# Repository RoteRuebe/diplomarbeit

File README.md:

Repository mit allen Files für die Diplomarbeit. An der Diplomarbeit arbeiten:

1. Lukas Lucut     (Hardware)
2. Bastian Eismann (3D - Modeling)
3. Yannick Zickler (Software)

---

# Hardware

Hier sind die Kicad - Platinendesigns von Roboter und Controller zu finden. Beide haben jeweils zwei Versionen, Rev A und Rev B.

# 3D - Modeling

Hier werden alle 3D Modelle und Cura 3D Setting sein.

# Software

Hier sind alle Codes der Diplomarbeit zu finden. Es gibt Testcodes für einzelne Module sowie die zusamengesetzten Hauptcodes

# Misc.

Außerdem sind die derzeitige Version der Diplomarbeit, Arbeitzeiterfassung (AZE) und der Projektplan hochgeladen.

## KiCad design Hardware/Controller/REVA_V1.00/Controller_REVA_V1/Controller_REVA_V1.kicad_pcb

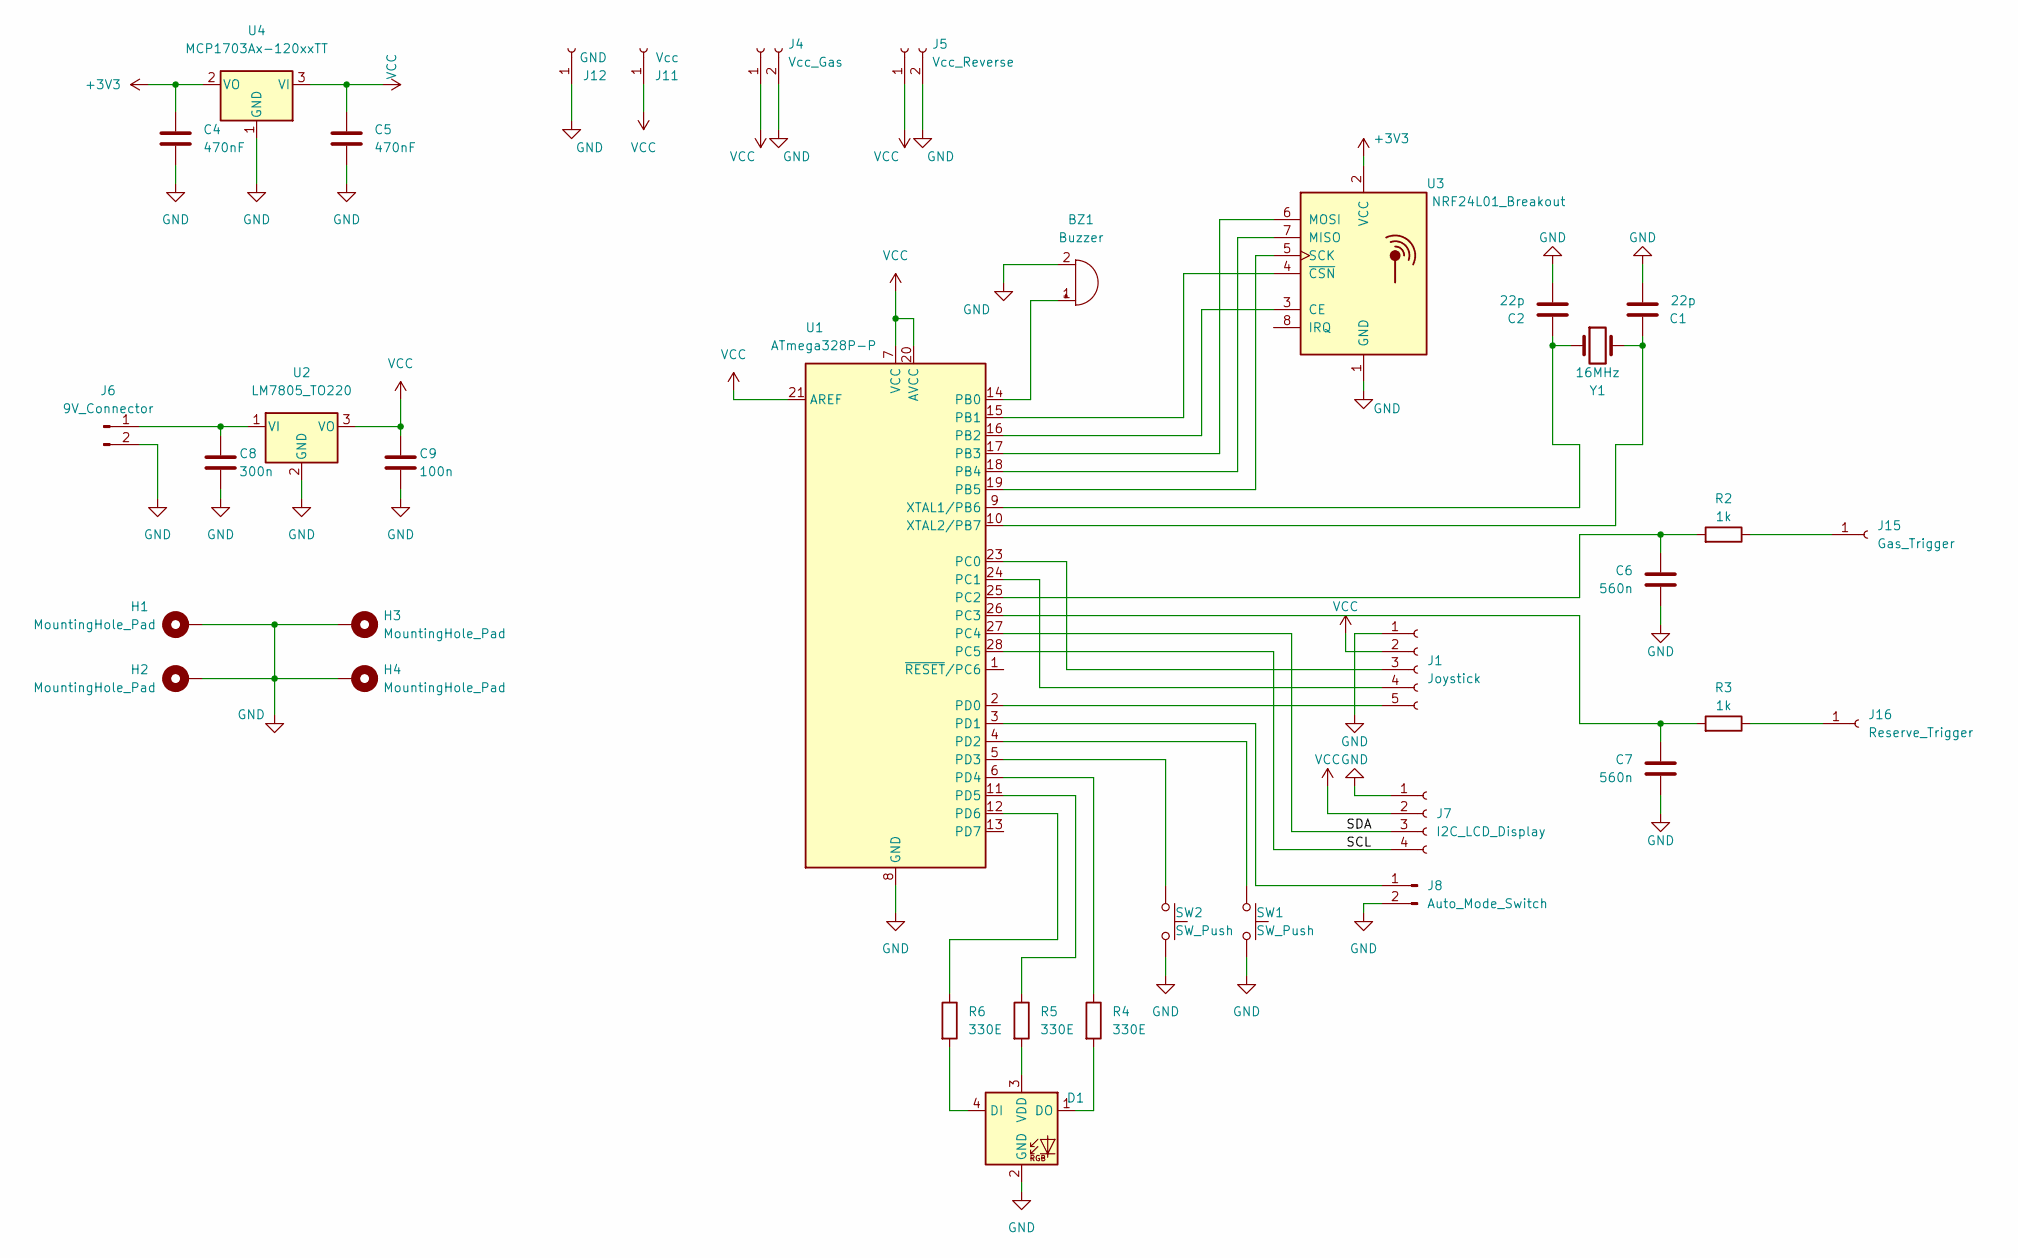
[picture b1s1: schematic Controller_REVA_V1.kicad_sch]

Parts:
BZ1: Buzzer; Buzzer_12x9.5RM7.6
C1, C2: 22p; C_1206_3216Metric
C4, C5: 470nF; C_1206_3216Metric
C6, C7: 560n; C_Disc_D12.5mm_W5.0mm_P7.50mm
C8: 300n; C_Disc_D12.5mm_W5.0mm_P7.50mm
C9: 100n; C_Disc_D12.5mm_W5.0mm_P7.50mm
D1: APA-106-F5; LED_D5.0mm-4_RGB
H1, H2, H3, H4: MountingHole_Pad; MountingHole_3.2mm_M3_Pad
J1: Joystick; PinHeader_1x05_P2.54mm_Vertical
J4: Vcc_Gas; PinHeader_1x02_P2.54mm_Vertical
J5: Vcc_Reverse; PinHeader_1x02_P2.54mm_Vertical
J6: 9V_Connector; PinHeader_1x02_P2.54mm_Vertical
J7: I2C_LCD_Display; PinHeader_1x04_P2.54mm_Vertical
J8: Auto_Mode_Switch; PinHeader_1x02_P2.54mm_Vertical
J11: Vcc; PinSocket_1x01_P2.54mm_Vertical
J12: GND; PinSocket_1x01_P2.54mm_Vertical
J15: Gas_Trigger; PinHeader_1x01_P2.54mm_Vertical
J16: Reserve_Trigger; PinHeader_1x01_P2.54mm_Vertical
R2, R3: 1k; R_Axial_DIN0411_L9.9mm_D3.6mm_P15.24mm_Horizontal
R4, R5, R6: 330E; R_1206_3216Metric
SW1, SW2: SW_Push; SW_PUSH-12mm_Wuerth-430476085716
U1: ATmega328P-P; DIP-28_W7.62mm
U2: LM7805_TO220; TO-220-3_Vertical
U3: NRF24L01_Breakout; nRF24L01_Breakout
U4: MCP1703Ax-120xxTT; SOT-23
Y1: 16MHz; Crystal_HC49-4H_Vertical

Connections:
+3V3: C4.1, U3.2 (VCC), U4.2 (VO)
/SCL: J7.4, U1.28 (PC5)
/SDA: J7.3, U1.27 (PC4)
GND: BZ1.2 (+), C1.2, C2.2, C4.2, C5.2, C6.2, C7.2, C8.2, C9.2, D1.2 (GND), H1.1, H2.1, H3.1, H4.1, J1.1, J4.2, J5.2, J6.2, J7.1, J8.2, J12.1, SW1.2, SW2.2, U1.8 (GND), U1.22 (GND), U2.2 (GND), U3.1 (GND), U4.1 (GND)
unnamed: BZ1.1 (-), U1.14 (PB0)
unnamed: C1.1, U1.10 (XTAL2/PB7), Y1.2
unnamed: C2.1, U1.9 (XTAL1/PB6), Y1.1
unnamed: C6.1, R2.2, U1.25 (PC2)
unnamed: C7.1, R3.2, U1.26 (PC3)
unnamed: C8.1, J6.1, U2.1 (VI)
unnamed: D1.1 (DO), R4.2
unnamed: D1.3 (VDD), R5.2
unnamed: D1.4 (DI), R6.2
unnamed: J1.3, U1.23 (PC0)
unnamed: J1.4, U1.24 (PC1)
unnamed: J1.5, U1.2 (PD0)
unnamed: J8.1, U1.3 (PD1)
unnamed: J15.1, R2.1
unnamed: J16.1, R3.1
unnamed: R4.1, U1.6 (PD4)
unnamed: R5.1, U1.11 (PD5)
unnamed: R6.1, U1.12 (PD6)
unnamed: SW1.1, U1.4 (PD2)
unnamed: SW2.1, U1.5 (PD3)
unnamed: U1.15 (PB1), U3.4 (~CSN)
unnamed: U1.16 (PB2), U3.3 (CE)
unnamed: U1.17 (PB3), U3.6 (MOSI)
unnamed: U1.18 (PB4), U3.7 (MISO)
unnamed: U1.19 (PB5), U3.5 (SCK)
VCC: C5.1, C9.1, J1.2, J4.1, J5.1, J7.2, J11.1, U1.7 (VCC), U1.20 (AVCC), U1.21 (AREF), U2.3 (VO), U4.3 (VI)

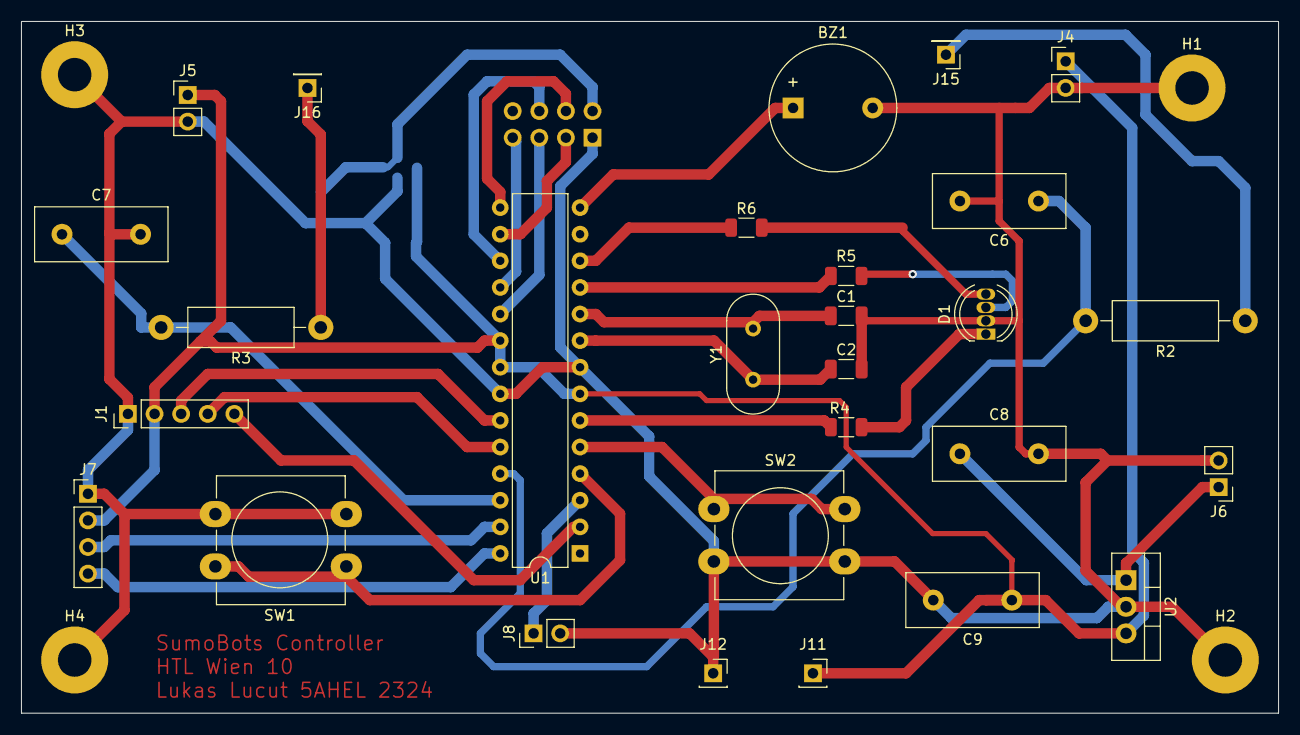
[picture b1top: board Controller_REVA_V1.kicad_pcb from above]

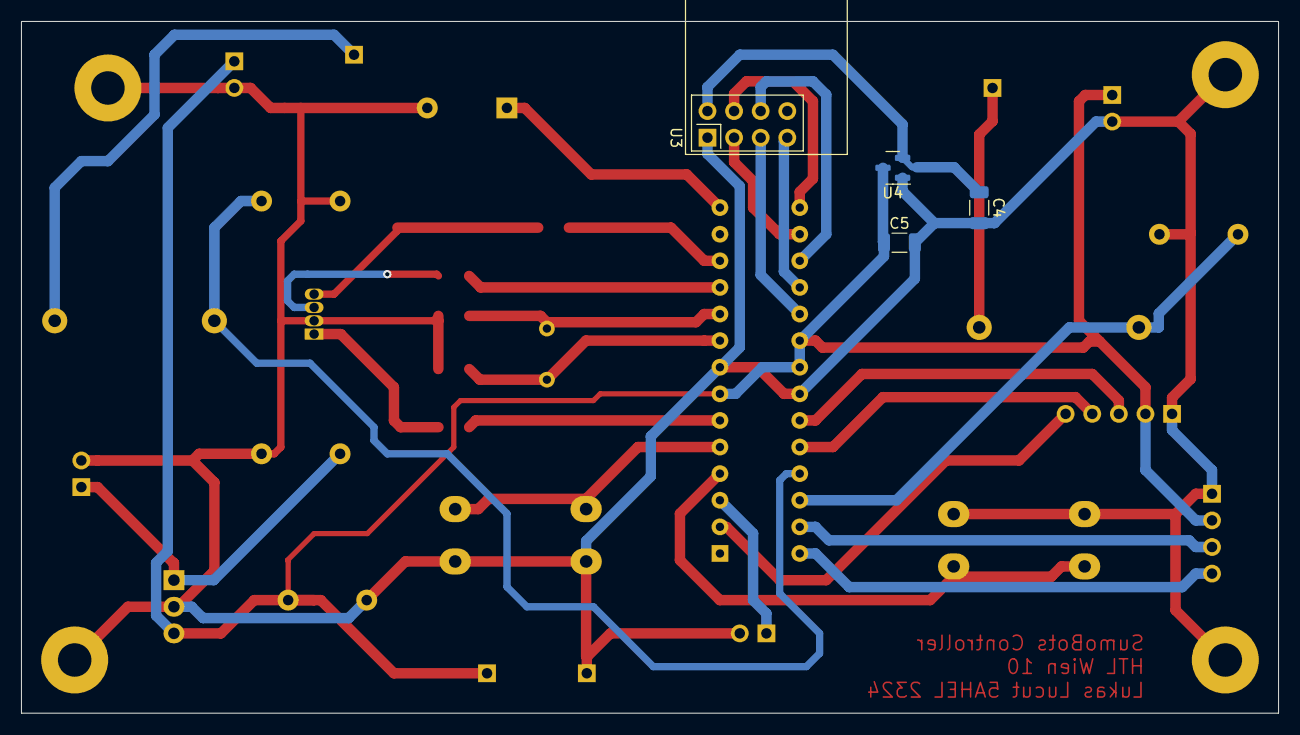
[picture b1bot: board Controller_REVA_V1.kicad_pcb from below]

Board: 2 copper layers, 120.0 x 66.0 mm, 36 parts (4 on the bottom side), 30 nets.

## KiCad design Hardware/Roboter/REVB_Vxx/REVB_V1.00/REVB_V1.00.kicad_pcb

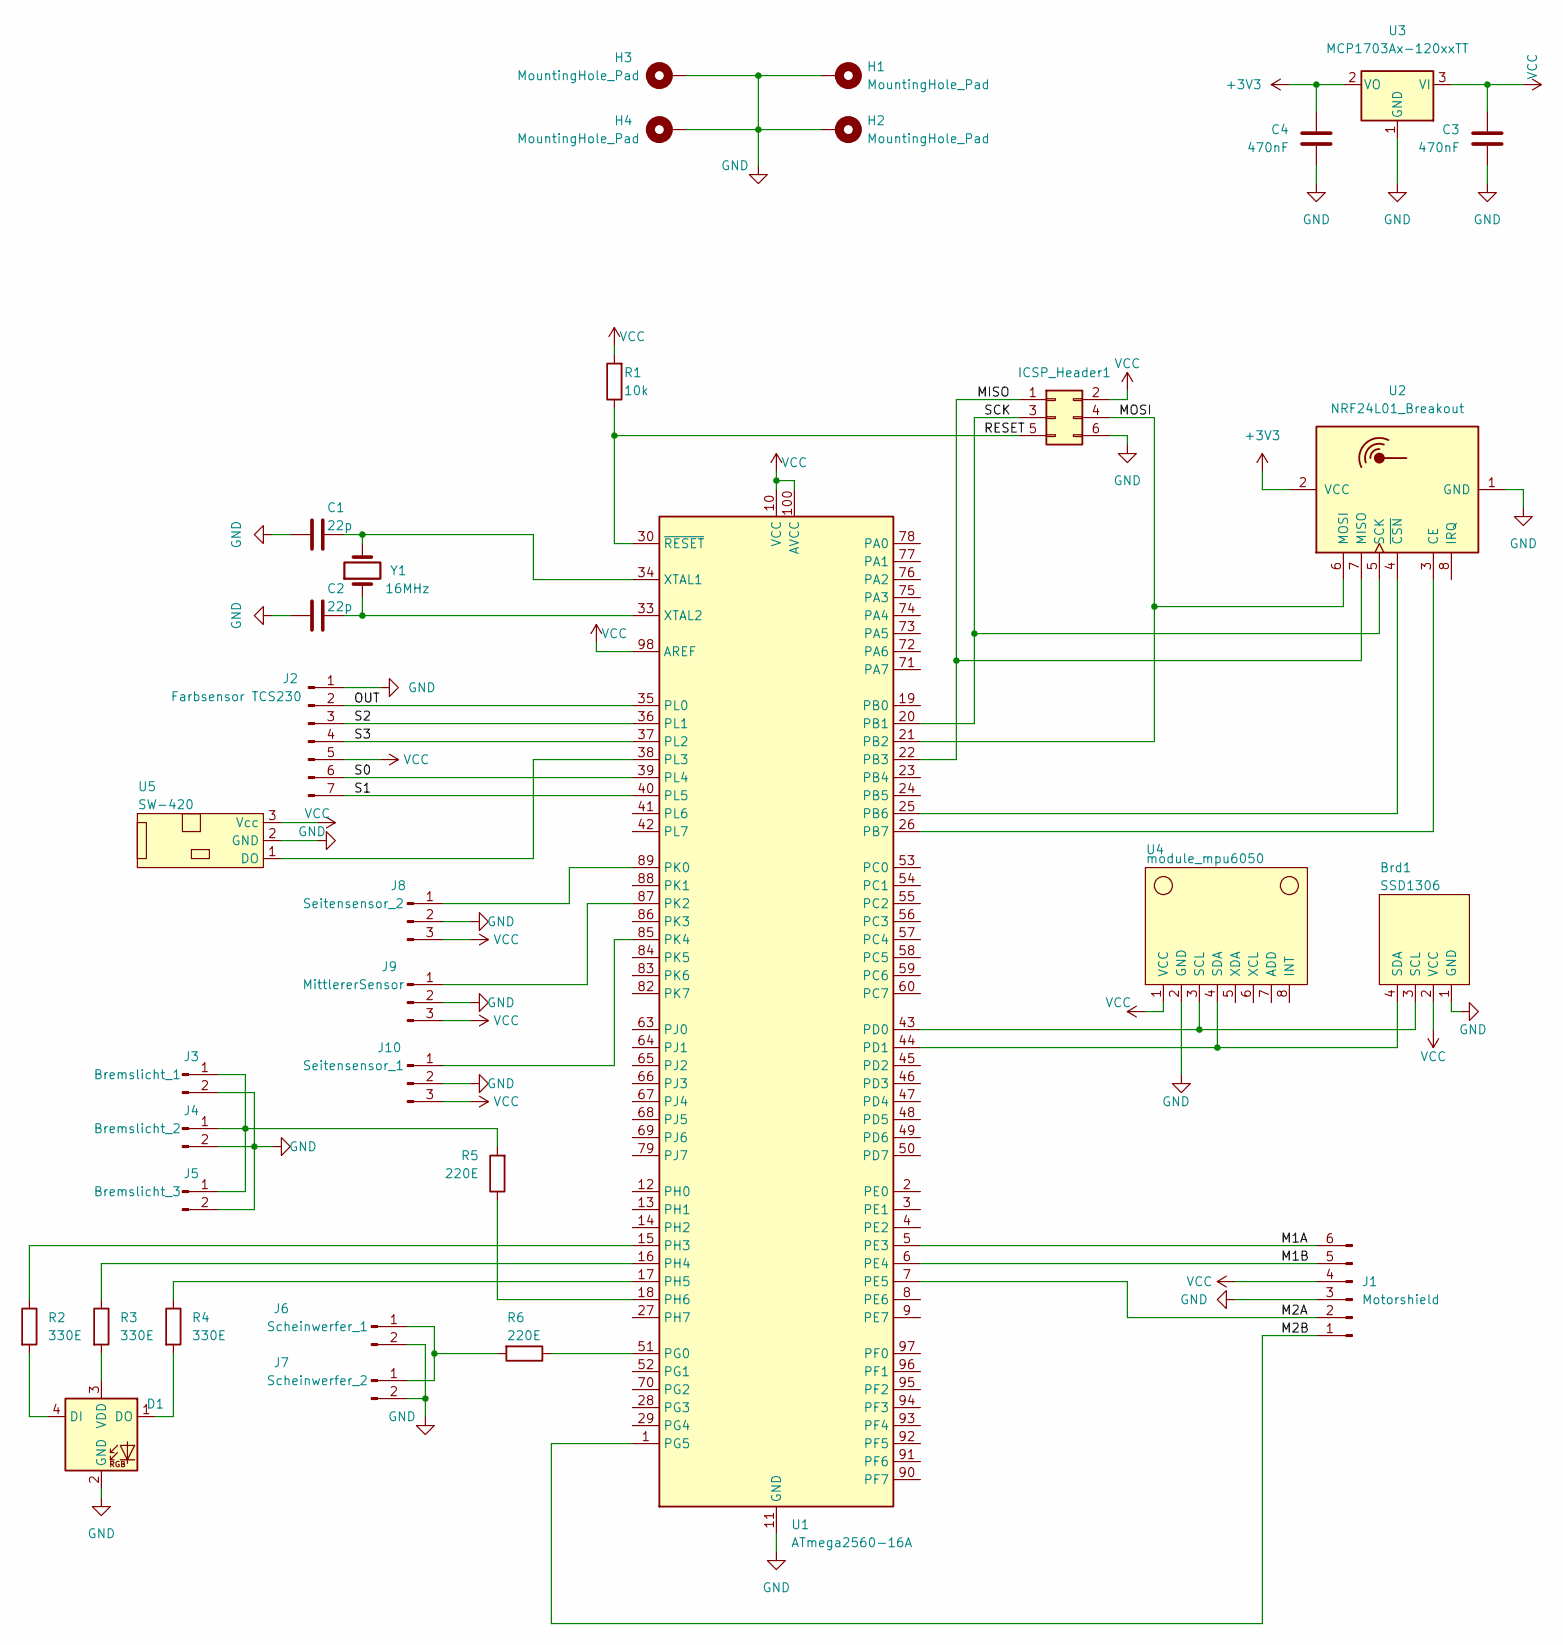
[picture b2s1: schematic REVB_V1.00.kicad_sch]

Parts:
Brd1: SSD1306; PinSocket_1x04_P2.54mm_Vertical
C1, C2: 22p; C_1206_3216Metric
C3, C4: 470nF; C_1206_3216Metric
D1: APA-106-F5; LED_D5.0mm-4_RGB
H1, H2, H3, H4: MountingHole_Pad; MountingHole_3.2mm_M3_Pad
ICSP_Header1: Conn_02x03_Odd_Even; PinHeader_2x03_P2.54mm_Vertical
J1: Motorshield; PinHeader_1x06_P2.54mm_Vertical
J2: Farbsensor TCS230; PinHeader_1x07_P2.54mm_Vertical
J3: Bremslicht_1; PinHeader_1x02_P2.54mm_Vertical
J4: Bremslicht_2; PinHeader_1x02_P2.54mm_Vertical
J5: Bremslicht_3; PinHeader_1x02_P2.54mm_Vertical
J6: Scheinwerfer_1; PinHeader_1x02_P2.54mm_Vertical
J7: Scheinwerfer_2; PinHeader_1x02_P2.54mm_Vertical
J8: Seitensensor_2; PinHeader_1x03_P2.54mm_Vertical
J9: MittlererSensor; PinHeader_1x03_P2.54mm_Vertical
J10: Seitensensor_1; PinHeader_1x03_P2.54mm_Vertical
R1: 10k; R_1206_3216Metric
R2, R3, R4: 330E; R_1206_3216Metric
R5, R6: 220E; R_1206_3216Metric
U1: ATmega2560-16A; TQFP-100_14x14mm_P0.5mm
U2: NRF24L01_Breakout; nRF24L01_Breakout
U3: MCP1703Ax-120xxTT; SOT-23
U4: module_mpu6050
U5: SW-420
Y1: 16MHz; Crystal_HC49-4H_Vertical

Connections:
+3V3: C4.1, U2.2 (VCC), U3.2 (VO)
/M1A: J1.6, U1.5 (PE3)
/M1B: J1.5, U1.6 (PE4)
/M2A: J1.2, U1.7 (PE5)
/M2B: J1.1, U1.1 (PG5)
/MISO: ICSP_Header1.1, U1.22 (PB3), U2.7 (MISO)
/MOSI: ICSP_Header1.4, U1.21 (PB2), U2.6 (MOSI)
/OUT: J2.2, U1.35 (PL0)
/RESET: ICSP_Header1.5, R1.1, U1.30 (~RESET)
/S0: J2.6, U1.39 (PL4)
/S1: J2.7, U1.40 (PL5)
/S2: J2.3, U1.36 (PL1)
/S3: J2.4, U1.37 (PL2)
/SCK: ICSP_Header1.3, U1.20 (PB1), U2.5 (SCK)
GND: Brd1.1 (GND), C1.2, C2.2, C3.2, C4.2, D1.2 (GND), H1.1, H2.1, H3.1, H4.1, ICSP_Header1.6, J1.3, J2.1, J3.2, J4.2, J5.2, J6.2, J7.2, J8.2, J9.2, J10.2, U1.11 (GND), U1.32 (GND), U1.62 (GND), U1.81 (GND), U1.99 (GND), U2.1 (GND), U3.1 (GND), U4.2 (GND), U5.2 (GND)
unnamed: Brd1.3 (SCL), U1.43 (PD0), U4.3 (SCL)
unnamed: Brd1.4 (SDA), U1.44 (PD1), U4.4 (SDA)
unnamed: C1.1, U1.34 (XTAL1), Y1.2
unnamed: C2.1, U1.33 (XTAL2), Y1.1
unnamed: D1.1 (DO), R4.2
unnamed: D1.3 (VDD), R3.2
unnamed: D1.4 (DI), R2.2
unnamed: J3.1, J4.1, J5.1, R5.2
unnamed: J6.1, J7.1, R6.2
unnamed: J9.1, U1.87 (PK2)
unnamed: J10.1, U1.85 (PK4)
unnamed: R2.1, U1.15 (PH3)
unnamed: R3.1, U1.16 (PH4)
unnamed: R4.1, U1.17 (PH5)
unnamed: R5.1, U1.18 (PH6)
unnamed: R6.1, U1.51 (PG0)
unnamed: U1.25 (PB6), U2.4 (~CSN)
unnamed: U1.26 (PB7), U2.3 (CE)
unnamed: U1.38 (PL3), U5.1 (DO)
unnamed: J8.1, U1.89 (PK0)
VCC: Brd1.2 (VCC), C3.1, ICSP_Header1.2, J1.4, J2.5, J8.3, J9.3, J10.3, R1.2, U1.10 (VCC), U1.31 (VCC), U1.61 (VCC), U1.80 (VCC), U1.98 (AREF), U1.100 (AVCC), U3.3 (VI), U4.1 (VCC), U5.3 (Vcc)

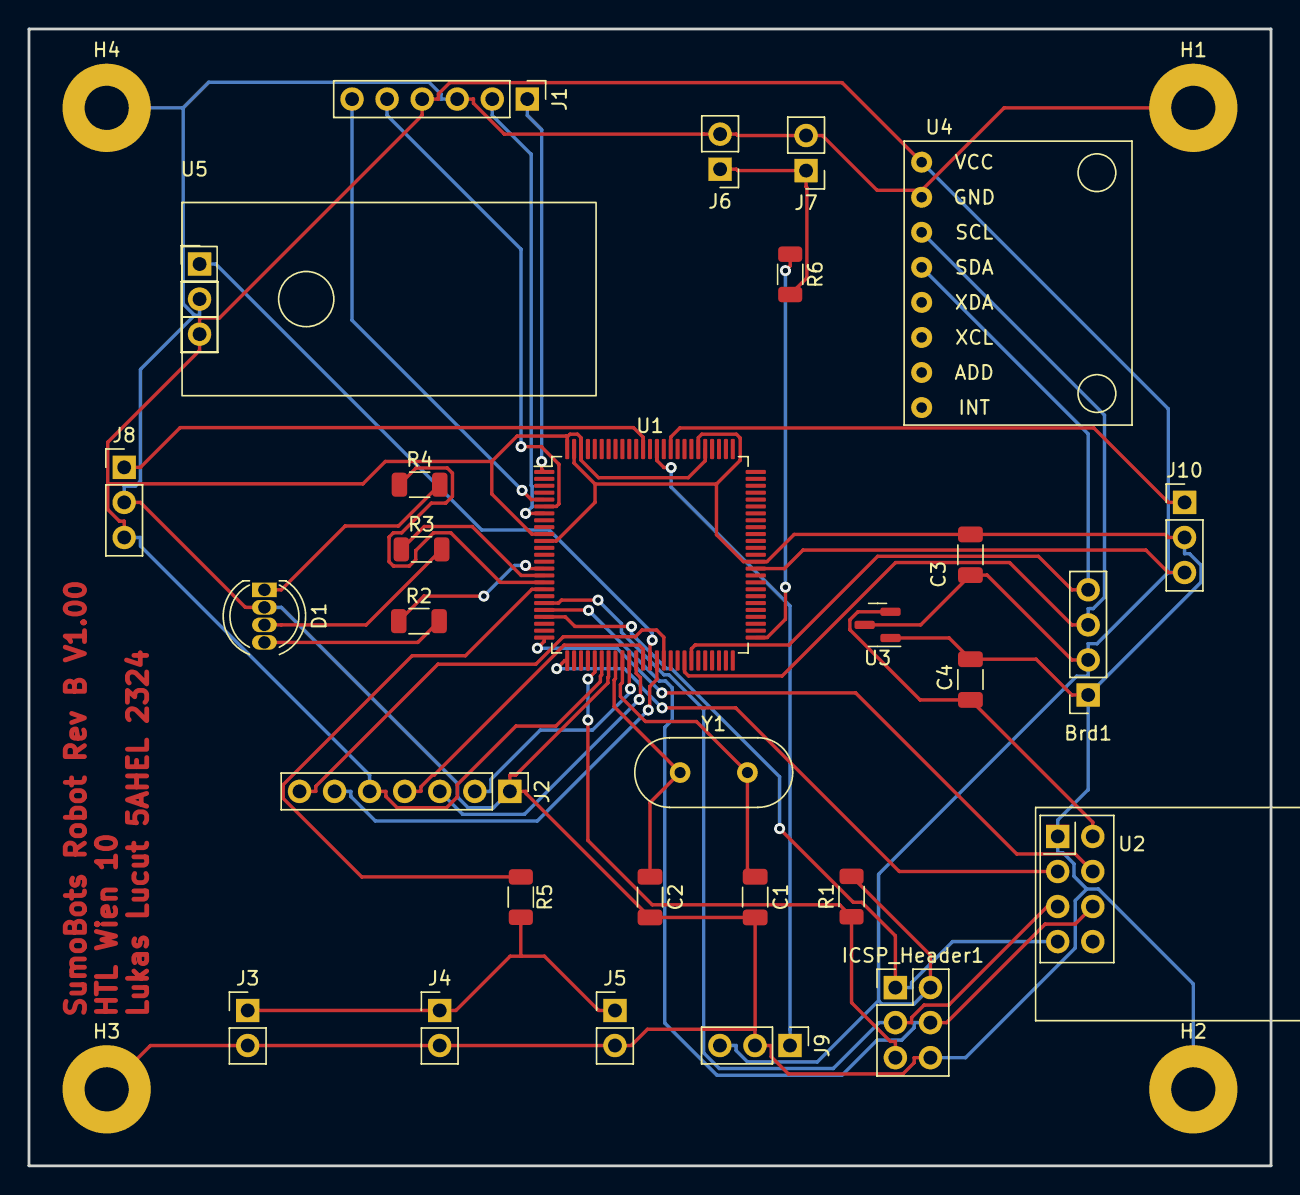
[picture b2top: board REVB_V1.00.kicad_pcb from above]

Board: 2 copper layers, 90.0 x 82.4 mm, 33 parts (0 on the bottom side), 36 nets.

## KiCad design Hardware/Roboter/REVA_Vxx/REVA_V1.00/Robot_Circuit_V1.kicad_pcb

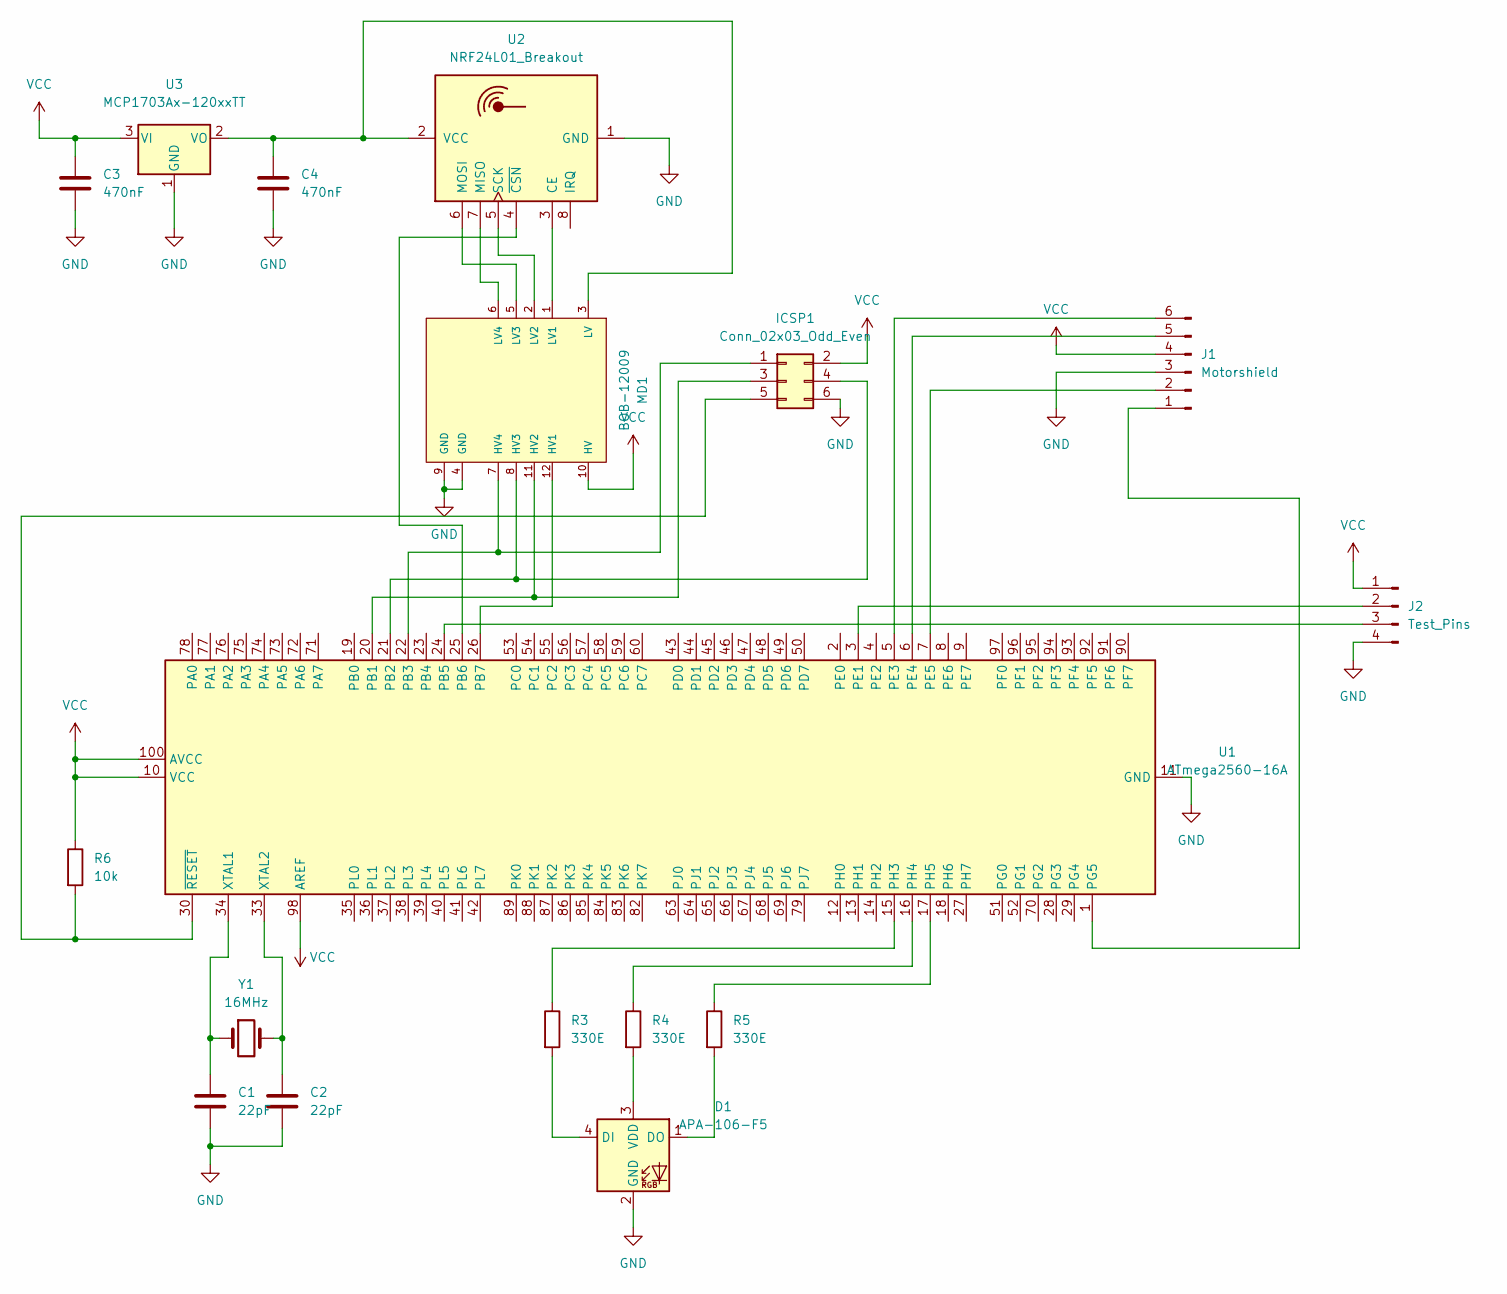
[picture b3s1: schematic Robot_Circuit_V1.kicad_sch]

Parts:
C1, C2: 22pF; C_1206_3216Metric
C3, C4: 470nF; C_1206_3216Metric
D1: APA-106-F5; LED_D5.0mm-4_RGB
ICSP1: Conn_02x03_Odd_Even; PinHeader_2x03_P2.54mm_Vertical
J1: Motorshield; PinHeader_1x06_P2.54mm_Vertical
J2: Test_Pins; PinSocket_1x04_P2.54mm_Vertical
MD1: BOB-12009; SparkFun-BOB-12009-MFG; mouser part number 474-BOB-12009; digikey description LOGIC LEVEL CONVERTER - BI-DIREC
R3, R4, R5: 330E; R_1206_3216Metric
R6: 10k; R_1206_3216Metric
U1: ATmega2560-16A; TQFP-100_14x14mm_P0.5mm
U2: NRF24L01_Breakout; nRF24L01_Breakout
U3: MCP1703Ax-120xxTT; SOT-23
Y1: 16MHz; Crystal_HC49-U_Vertical

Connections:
unnamed: C1.1, U1.34 (XTAL1), Y1.1
unnamed: C2.1, U1.33 (XTAL2), Y1.2
unnamed: C4.1, MD1.3 (LV), U2.2 (VCC), U3.2 (VO)
unnamed: D1.1 (DO), R5.2
unnamed: D1.3 (VDD), R4.2
unnamed: D1.4 (DI), R3.2
unnamed: ICSP1.1, MD1.7 (HV4), U1.22 (PB3)
unnamed: ICSP1.3, MD1.11 (HV2), U1.20 (PB1)
unnamed: ICSP1.4, MD1.8 (HV3), U1.21 (PB2)
unnamed: ICSP1.5, R6.2, U1.30 (~RESET)
unnamed: J1.1, U1.1 (PG5)
unnamed: J1.2, U1.7 (PE5)
unnamed: J1.5, U1.6 (PE4)
unnamed: J1.6, U1.5 (PE3)
unnamed: J2.2, U1.3 (PE1)
unnamed: J2.3, U1.24 (PB5)
unnamed: MD1.1 (LV1), U2.3 (CE)
unnamed: MD1.2 (LV2), U2.5 (SCK)
unnamed: MD1.5 (LV3), U2.6 (MOSI)
unnamed: MD1.6 (LV4), U2.7 (MISO)
unnamed: MD1.12 (HV1), U1.26 (PB7)
unnamed: R3.1, U1.15 (PH3)
unnamed: R4.1, U1.16 (PH4)
unnamed: R5.1, U1.17 (PH5)
unnamed: U1.25 (PB6), U2.4 (~CSN)
VCC: C3.1, ICSP1.2, J1.4, J2.1, MD1.10 (HV), R6.1, U1.10 (VCC), U1.31 (VCC), U1.61 (VCC), U1.80 (VCC), U1.98 (AREF), U1.100 (AVCC), U3.3 (VI)

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
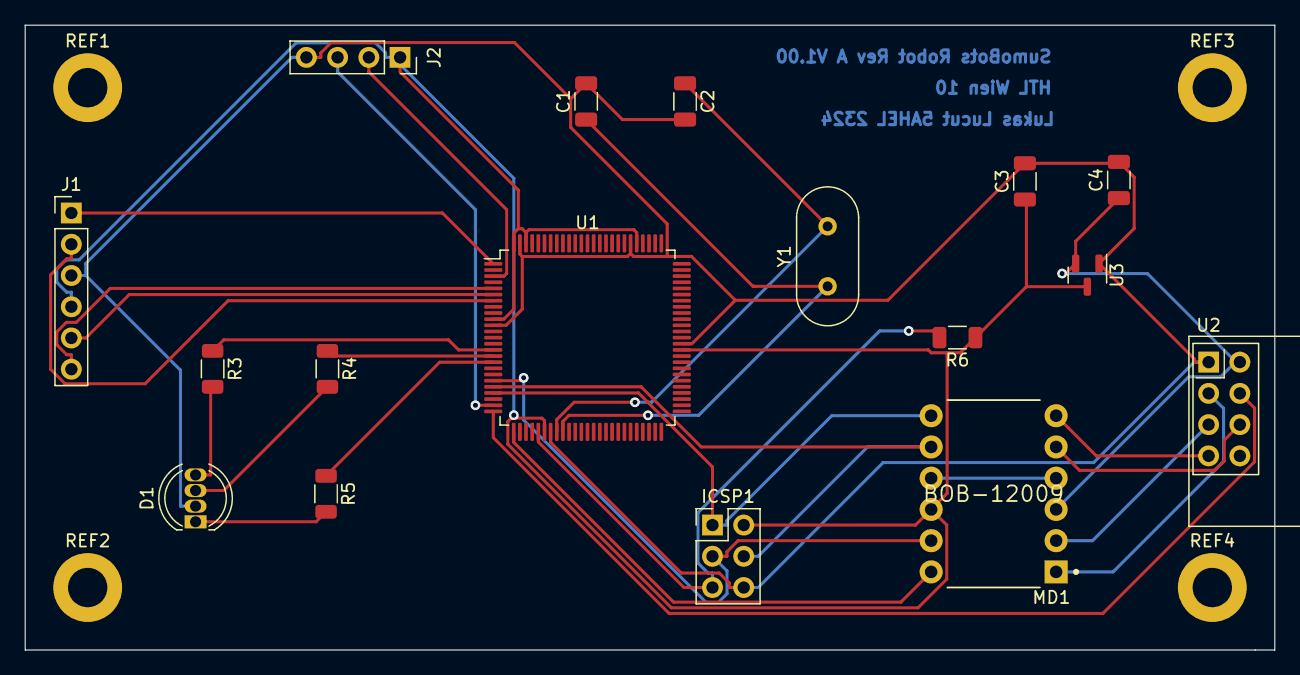
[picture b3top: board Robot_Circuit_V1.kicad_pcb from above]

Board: 2 copper layers, 101.6 x 50.8 mm, 21 parts (0 on the bottom side), 28 nets.

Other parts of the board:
REF1, REF2, REF3, REF4: MountingHole_3.2mm_M3_DIN965_Pad

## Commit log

2023-12-11 Initial Commit - moving files from google drive to github
2023-12-11 Cleaning up and adding "Projektplan"
2023-12-12 test Zugriffsberechtigung
2023-12-12 neue Inhalte Quarzoszillator
2023-12-14 Neue Dokumentation
2023-12-14 Kapitel 6 Begonnen
2023-12-14 Codes updaten für Kommunikation mit zentralem Server
2023-12-15 Cleaning up code, adding header file
2023-12-15 neue Überschriften, HW-Teil
2023-12-15 bearbeitete Version
2023-12-15 AZE, stand 15.12.2023 13:53
2023-12-15 Kleine Verbesserung
2023-12-15 neue Projektstatusdoku. für Projektlibre
2023-12-15 Weekly-Report-System neu aufgesetzt, jeden Samstag wird die neuste Datei abgegeben
2023-12-15 PLA Dokumentation
2023-12-15 Fehler Ausgebessert 3D-Design
2023-12-16 +3D-Modell Zeug UwU
2023-12-16 Weekly Report 10 auch hier lmao
2023-12-16 NRF24L01+ Teil fertiggeschrieben, wird 16.12.2023 abgegeben
2023-12-16 abgegeben, 16-12-2023
2023-12-16 Fehler ausgebessert
2023-12-26 AZE aktualisiert
2023-12-27 AZE aktualisiert, Rev B fertig und Zatl geschickt (27.12.2023, 18:24:21)
2023-12-27 AZE nochmal, hab was vergessen
2024-01-07 Dokumentation, HW -> Rev A fertig dokumentiert, Rev B Blockschaltbild hinzugefügt
2024-01-09 Rev B Dokumentation, noch nicht fertig fehlt bissl was
2024-01-09 HW-Teil erweitert yuuhuu
2024-01-09 3D Material Fertig
2024-01-12 HW-Teil, Rev B PCB Kapitel fertig :)
2024-01-13 Add files via upload
    Kleine Überarbeitung
2024-01-13 Server code
2024-01-13 AZE stand 19:32:49, 13:01:2024
2024-01-13 DA umbenannt
2024-01-15 Mehr 3 D Print 👌
2024-01-15 Version gerettet <3
2024-01-19 code verschieben
2024-01-19 Updated text.jpg
2024-01-19 Neue Version lmao
2024-01-20 abgegeben
2024-01-20 alte version le deleted
2024-01-22 Zatl korrigierte Version 1.3
2024-01-23 no message
2024-01-25 testetetet
2024-01-26 Deleting useless files
2024-01-26 Uploading server code
2024-01-26 I2C-Bus
2024-01-26 Deleting log files, new Server code
2024-01-26 New Robo code
2024-01-28 More comments
2024-01-28 Das internet ist fuer uns alle neuland. Erweiterung website
2024-01-28 Very minor fix
2024-01-28 Neues icon
2024-01-28 Rounded boxes!
2024-01-30 Neuer server code. Nicht fertig, Roboter code muss angepasst werden. Außerdem: pfadänderung der logs noch nicht in allen codes übernommen.
2024-01-31 AZE aktualisiert 😎, verbesserte Version der DA hochgeladen 🦁
2024-02-02 Reverting prev Commit.
2024-02-02 Revert "Reverting prev Commit." ups.
    This reverts commit 57b0e3b5c6768b9112b4db4ac3e3c5eee2560ce9.
2024-02-02 anpassung map funktion auf fmap. verbindung zw. roboter und controller und roboter und server funktioniert noch nicht gleichzeitig, jetzt verbindung zw. roboter und server auskommentiert. typecasting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
2024-02-03 Files umbennant. Roboter code refactored Alle Files wurden auf lowercase gestellt
    Roboter Code Reihenfolge von Read / Write und stopListening umgestellt. Vielleicht geht das ja jetzt. Auserdem Aenderung Read pipe von 0 auf 1. Funktioniert read() und isAvailable() trotzdem gleich?
    Refactoring von Variablennamen, Ort der Deklaration in roboter.ino und roboter.h
2024-02-03 Upload der Aenderungen des letzten commits
2024-02-03 AZE aktualisiert, Farbsensor und OLED-Display dokumentiert
2024-02-08 korrigierte Version von ZATL
2024-02-08 AZE aktualisiert 😜, Infrarotsensor dokumentiert Komponente von Rev B sind fertig
2024-02-10 AZE aktualisiert, WR 20
2024-02-10 Quellenverzeichnis/Literaturverzeichnis befüllt, Schaltungen u. PCB in Anhängen hinzugefügt
2024-02-13 Bug fixes
    Version geht noch immer nicht
2024-02-13 Bugfixes
    Berechnung für Motorsteuerung. Kom. hatte Fehler, nun auskommentiert.
2024-02-15 AZE aktualisiert 🔞
2024-02-16 Salvation
    Kom. mit Server und Controller funktioniert gleichzeitig. So kompliziert war die Lösung eh nicht 🙃
2024-02-16 Debug statement gelöscht
2024-02-16 Implementierung Gyroskop. Noch nicht vollständig
2024-02-16 PM-Dokumentation wurde gestartet --> Sotftwareverwaltung via Git
2024-02-16 AZE aktualisiert Never gonna Give u up 🤣
2024-02-17 AZE optisch bearbeitet, Diplomarbeit PM-Teil umformuliert
2024-02-18 DA V1.6 Korrektur
2024-02-18 Dokumentation Server und Protokoll zw. Roboter und Server. Hinzufügung der Codes in den Anhang
2024-02-18 Änderung von Zatl, Kapitel 9.2
2024-02-19 Code: Implementation Gyroskop
    Änderung von Server und Roboter Code. Noch ungetestet.
2024-02-19 Neues Cooles Kapitel
2024-02-19 Code: Bugfixes in implementierung von Gyroskop
    Problem: Im Gyroskop Datenpacket werden zu viele Bytes gesendet, das RF24 Modul kann max. 32 senden.
    To Do: Aufteilen des Packets in Acc, Gyro und Temp um das zu vermeiden
2024-02-19 Bugfixes für Gyroskop Roboter-seitig
2024-02-19 Code: Bugfix Gyroskop
    Die Packete des Gyroskops werden aufgeteilt, um das 32 Byte-limit des RF24 Moduls nicht zu erreichen.
2024-02-19 Code: Weis nicht mehr. Iwas gyroskop diagram usw.
2024-02-19 Code: mini Änderung jo
2024-02-19 kurz was umgeschrieben 😐
2024-02-20 Code: Sensor data are floats not ints now
2024-02-20 Code: Einige Änderungen in Roboter
    1. Array wird zwischen jedem Versenden mit clearDataArray komplett gelöscht.
    2. Check, ob Gyro auch angeschlossen wurde -> Fehler in Elektronik wurde aufgedeckt
    3. LED wird runtime geupdated, wenn er sich mit dem Server verbindet
2024-02-20 Gyrskop eingeführt
2024-02-20 Einen Satz geschrieben 😋
2024-02-20 Neue Inhalte in DA: softwareteil
2024-02-20 AZE (auf Gönnungtour) aktualisiert, Controller Blockschaltbild eingefügt
2024-02-21 Neue INhalte Software
2024-02-22 Neue inhalte DA + kinderliechte kuhle kopfzeile
2024-02-22 AZE aktualisiert :^)
2024-02-23 flask server squash later
2024-02-23 Anstelle von python, txt files und php gibt es jetzt einen Multithreaden Flask Server
2024-02-23 Now running 1 Multithreaded Python Flask server instead of python for rf24 + php for webserver
2024-02-23 Revert "merging"
    This reverts commit bf34cdf9def5635425216a1e9576eeff1efccdaf, reversing
    changes made to 7d91e4d6d1b951679c960df9d1e7a7bc1c21a0f7.
2024-02-23 Renaming index.php to index.html
2024-02-23 Deleting index.php
2024-02-23 AZE und DA Dokumentation
2024-02-24 Code: Verbesserung Server Flask Server returned jetzt Daten. Diese kommen aus dem deque, welche hier als Ringpuffer verwendet werden Die Daten sind nichtmehr Textfiles sondern JSON
    Client Seitig sind die Requests jetzt asynchron, deswegen braucht es die callback funktionen
    Um nicht 20 callback funktionen zu haben, werden gyro xyz und acc xyz jetzt gleichzeitig abgefragt, was eh mehr sinn macht.
    Das heißt, server returned jetzt 2d array bei /data/gyro oder /acc. ahja statt /log gibt es jetzt /data
2024-02-24 Fixing typos
2024-02-24 Code: /data returns dict not 2d array. style.css fixed identation. replaced write_log with array.append. Added /about page
2024-02-26 AZE aktualisiert stand 26.02.2024
2024-02-27 Code: Minor changes to website
2024-02-28 Null bytes entfernen. Charts jetzt mit 10 fps.
2024-02-28 Graph jetzt 10 fps
2024-02-28 AZE aktualisiert 😎
2024-02-29 Version 2.1
2024-03-01 Code: Adding robotConnected to dashboard
2024-03-01 Small bugfix
2024-03-01 Code: Controller Anzeige implementiert
2024-03-01 AZE und HW-Teil erweitert
2024-03-03 Änderungen Server 1. Navbar hinzugefügt 2. Ein Diagramm entfernt 3. Tweaking einiger Margins, Colors etc.
2024-03-03 Neue Inhalte Software sowie kleine Änderungen Code
2024-03-03 Änderung pos. HTL logo
2024-03-04 AZE für Week 27 geöffnet, Montag eingetragen
2024-03-05 korrigierte Version von ZATL V1.8, noch zwei Versionen bis Sense ☠
2024-03-06 Controller setup protokoll
2024-03-06 AZE aktualisiert 😶
2024-03-07 AZE aktualisiert 😋
2024-03-08 HW-Controller und Doc.
2024-03-09 Added RGB-Spport for controller
2024-03-09 HW-Teil fertiggeschrieben (Raspi Zero u. ESP32 fehlt, wird bei korrekte Inbetriebnahme Dok.)
2024-03-12 Projektarchitektur u. Danksagung verfasst
2024-03-13 "upgedatet"
2024-03-14 AZE aktualisiert & Sensornutzen dokumentiert
2024-03-15 AZE + Dok
2024-03-18 DA Version 2.0 letzter Lauf
2024-03-18 Dok. + AZE
2024-03-19 Dokumentation :)
2024-03-19 HW-Dokumentation auf den neusten Stand
2024-03-20 AZE aktualisiert, Dok: PCB u. Circuit im Anhang, neues OSP
2024-03-20 Deleting debug msg controller.ino
2024-03-21 Channel, pipe as arg for multithreading
2024-03-21 Adding support for multiple robots/ controllers, make sendSensorData non-blocking
2024-03-21 Documentation channels / pipes
2024-03-21 AZE aktualisiert, Dokumentation: neues PSP, Roboter Rev A fertig, Controller Rev A fertig --> Rev B finale Ergebnisse mit Sensoren
2024-03-22 Small bugfixes
2024-03-22 Neue Inhalte
2024-03-22 Änderungen für Zulassung mehrerer Roboter
2024-03-22 Moving files
    Adding files back again
2024-03-23 AZE homies
2024-03-23 Neue Inhalte DA
2024-03-23 Support für mehrere Roboter in Website implementiert
2024-03-23 Deleting startup.sh
2024-03-23 Umbennenung pipes
2024-03-24 AZE++; Dok: PM-Inhalte, neues Abstract; Bedienungsanleitung: Draft
2024-03-24 HW-Teil 100% fertig u. formatiert, Unterüberschriften korrigiert, Endergebnisse DRAFT gestartet
2024-03-26 Frequenzmultiplex - es geht aber nicht sehr gut
2024-03-26 Frequenzmultiplex
2024-03-26 Typos
2024-03-27 Verbesserung Server statt startWrite verwendung von write mit weniger retries Dadurch blockiert radio.write() nur noch 10ms, nicht 60ms Außerdem rekonfiguration des Radiomoduls wenn dieses zB ab- und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
    Todo: Gleiche Änderungen im Server
    Todo: Versch. Module ansteuern
2024-03-28 Neue inhalte DA Software
2024-03-28 Teil 3D-Shit hinzugefügt
2024-03-28 formatiert
2024-03-31 Inhalte software funk autom. configuration
2024-04-01 Fotos, RGB-Status u. Server aufsetzen fehlen
2024-04-01 Korrektur von Zatl, neuer Ganttchart, AZE aktualisiert
2024-04-02 BC, AZE, Dok
2024-04-02 Abstract
2024-04-02 dok.
2024-04-02 askdfjsdflkjbg
2024-04-02 ndhflb
2024-04-03 Änderungen Pipenamen sodass nur erster Byte anders
2024-04-03 small aze update
2024-04-03 Änderung Variablennamen nach Styleguide & kleine Änderungen
2024-04-03 Inshallah es funktioniert. Statt strings jetzt structs verwendet. Reduktion der benötigten Datenrate um 80% !
2024-04-04 Module in Code hinzugefügt. Kleinigkeiten verbessert. Änderung in Server von Big auf Little Endian kommt morgen, ist im Raspberry
2024-04-05 Struct supprt Server
2024-04-05 AZE + Dok.
2024-04-05 3D Shematics angehangen
2024-04-05 Bedienungsanleitung FERTIG, Dok fertig --> SW fehlt
2024-04-06 Das Lebenswerk ist vollbracht.
2024-04-06 finished
2024-04-07 formatiert und pdf erstellt
2024-04-08 finished 2
2024-04-09 Farbkopien sind teuer.
2024-04-16 bitmap :3
2024-04-19 Inkludiere Bitmaps
2024-04-19 Lösche alles, was nicht sourcecode ist
2024-04-19 Lösche noch mehr
